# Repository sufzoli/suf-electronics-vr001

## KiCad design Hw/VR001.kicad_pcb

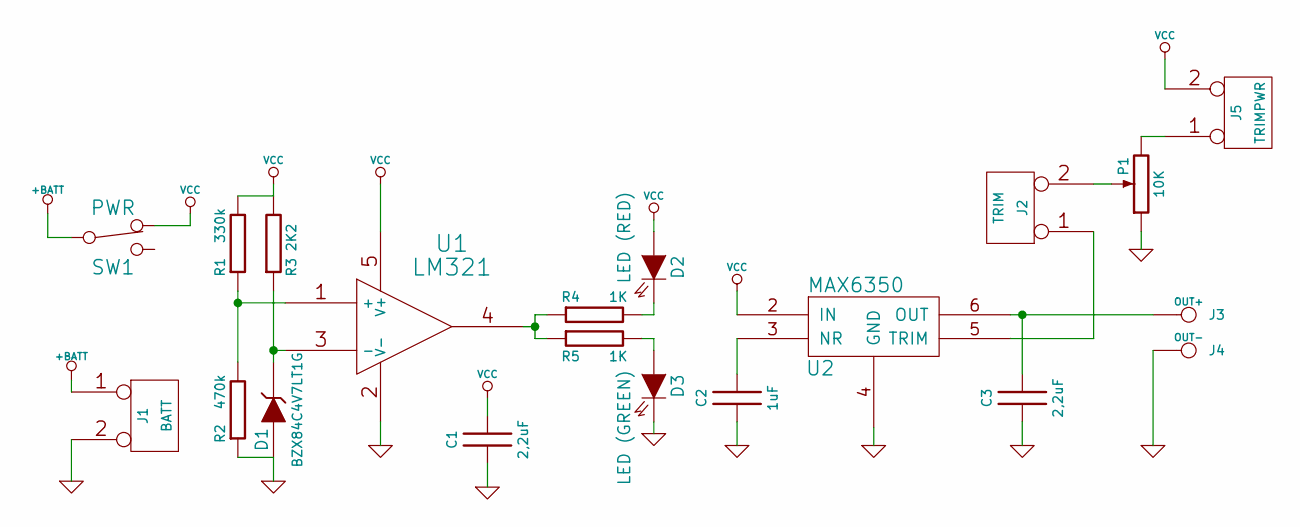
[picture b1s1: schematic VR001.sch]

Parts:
C1, C3: 2,2uF; SM0603
C2: 1uF; SM0603
D1: BZX84C4V7LT1G; SOT23
D2: LED (RED); SM1206
D3: LED (GREEN); SM1206
J1: BATT; HDR-2-EDGE
J2: TRIM; HDR-2-EDGE
J3: OUT+; BANANA_JACK
J4: OUT-; BANANA_JACK
J5: TRIMPWR; HDR-2-EDGE
P1: 10K; RV_BOU3296X-EDGE
R1: 330k; SM0603
R2: 470k; SM0603
R3: 2K2; SM0603
R4, R5: 1K; SM0603
SW1: PWR; SW_EDGE
U1: LM321; SOT23-5
U2: MAX6350; SOIC-8

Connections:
+BATT: J1.1, SW1.2
GND: C1.2, C2.2, C3.2, D1.1 (A), D3.2 (K), J1.2 (PM), J4.1, P1.1, R2.2, U1.2 (V-), U2.4 (GND)
unnamed: C3.1, J3.1, U2.6 (OUT)
unnamed: J5.1, P1.3
unnamed: J2.1, U2.5 (TRIM)
unnamed: J2.2 (PM), P1.2
unnamed: C2.1, U2.3 (NR)
unnamed: D2.2 (K), R4.1
unnamed: D1.3 (K), R3.2, U1.3 (-)
unnamed: R1.2, R2.1, U1.1 (+)
unnamed: R4.2, R5.2, U1.4
unnamed: D3.1 (A), R5.1
VCC: C1.1, D2.1 (A), J5.2 (PM), R1.1, R3.1, SW1.1, U1.5 (V+), U2.2 (IN)

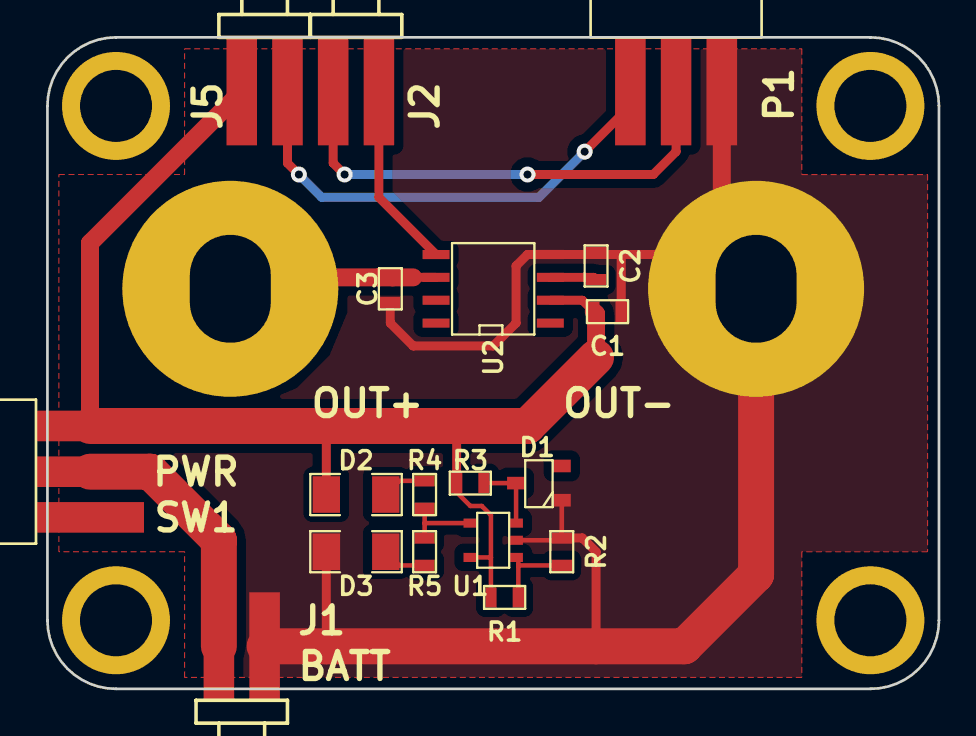
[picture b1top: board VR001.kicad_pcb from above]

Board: 2 copper layers, 49.5 x 36.2 mm, 24 parts (0 on the bottom side), 13 nets.

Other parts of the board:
MNT_HOLE_4, MNT_HOLE_4#2, MNT_HOLE_4#3, MNT_HOLE_4#4: Val**; MNT_HOLE_4

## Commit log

2013-12-18 Hardware design added
2021-03-20 Add remaining - archive
